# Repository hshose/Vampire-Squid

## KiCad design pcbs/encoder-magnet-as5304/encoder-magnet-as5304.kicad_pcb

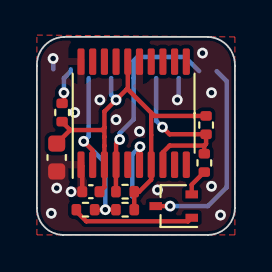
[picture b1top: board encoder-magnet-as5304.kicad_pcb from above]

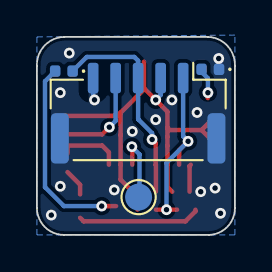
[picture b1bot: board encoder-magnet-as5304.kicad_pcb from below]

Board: 2 copper layers, 11.0 x 11.0 mm, 14 parts (4 on the bottom side), 10 nets.

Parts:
C1: 100n; C_0402_1005Metric
C2: 10µ; C_0603_1608Metric
D1: Red; LED_0402_1005Metric
D2: Blue; LED_0402_1005Metric
J1: BM05B-GHS; JST_GH_BM05B-GHS-TBT_1x05-1MP_P1.25mm_Vertical
Q1: BC807-40LWX; SOT-323_SC-70
R1, R2, R3: 1k; R_0402_1005Metric
R4: 47k; R_0402_1005Metric
R5, R6: 4k7; R_0402_1005Metric
TP1: AGC out; TestPoint_Pad_D1.5mm
U1: AS5304; TSSOP-20_4.4x6.5mm_P0.65mm

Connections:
+5V: C1.1, C2.1, J1.2, R1.1, R2.1, R3.1, R6.1, U1.3 (VDDP), U1.7 (VDD), U1.16 (VDDA)
/A: J1.1, R1.2, R4.1, U1.2 (A)
/B: D1.1 (K), J1.3, R2.2, U1.4 (B)
/I: J1.4, R3.2, R5.1, U1.8 (I)
GND: C1.2, C2.2, D2.1 (K), J1.5, J1.MP (MountPin), U1.1 (VSS), U1.15 (TEST_GND), U1.20 (ZPZ)
unnamed: D1.2 (A), Q1.3 (C)
unnamed: D2.2 (A), R6.2
unnamed: Q1.1 (B), R4.2
unnamed: Q1.2 (E), R5.2
unnamed: TP1.1, U1.6 (AO)

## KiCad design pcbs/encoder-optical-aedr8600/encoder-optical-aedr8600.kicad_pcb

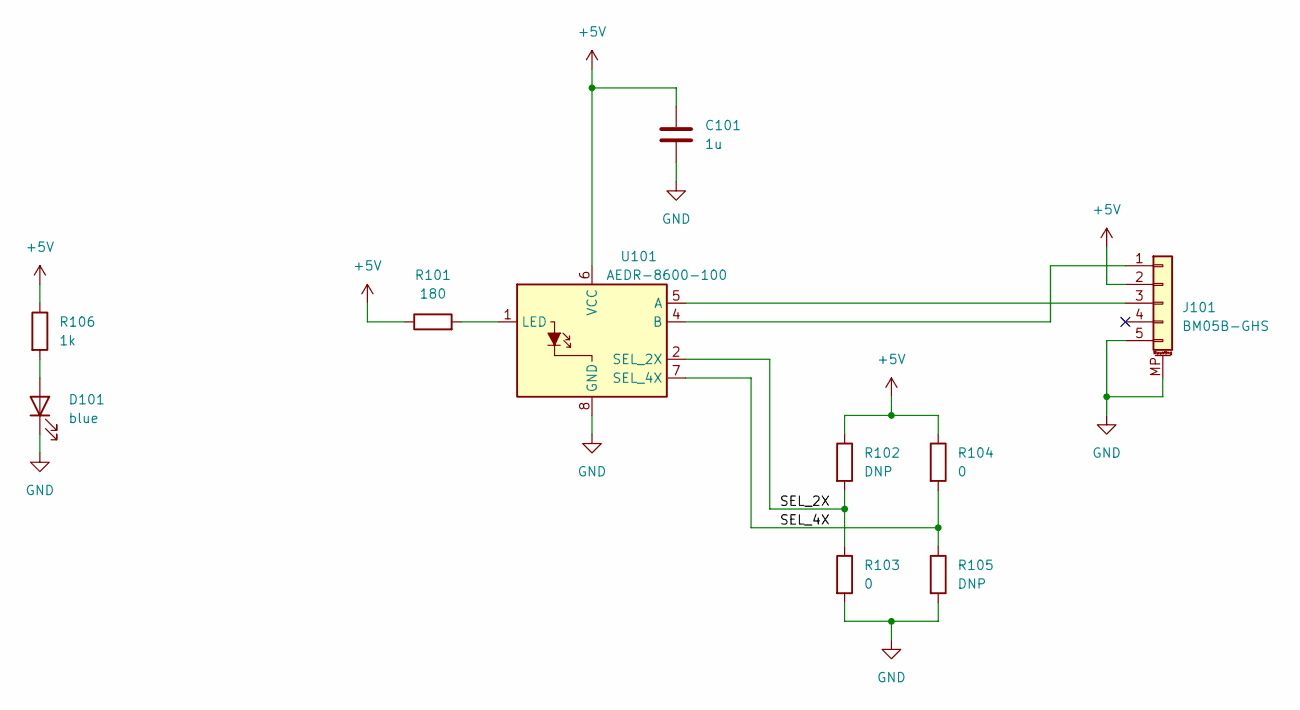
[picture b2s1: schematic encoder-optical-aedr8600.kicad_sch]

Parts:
C101: 1u; C_0402_1005Metric
D101: blue; LED_0402_1005Metric
J101: BM05B-GHS; JST_GH_BM05B-GHS-TBT_1x05-1MP_P1.25mm_Vertical
R101: 180; R_0402_1005Metric
R102, R105: DNP; R_0402_1005Metric
R103, R104: 0; R_0402_1005Metric
R106: 1k; R_0402_1005Metric
U101: AEDR-8600-100; AEDR-8600

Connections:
+5V: C101.1, J101.2, R101.1, R102.1, R104.1, R106.1, U101.6 (VCC)
/SEL_2X: R102.2, R103.1, U101.2 (SEL_2X)
/SEL_4X: R104.2, R105.1, U101.7 (SEL_4X)
GND: C101.2, D101.1 (K), J101.5, J101.MP (MountPin), R103.2, R105.2, U101.8 (GND)
unnamed: D101.2 (A), R106.2
unnamed: J101.1, U101.4 (B)
unnamed: J101.3, U101.5 (A)
unnamed: R101.2, U101.1 (LED)

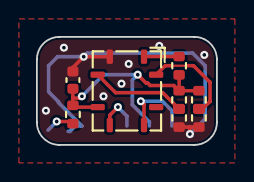
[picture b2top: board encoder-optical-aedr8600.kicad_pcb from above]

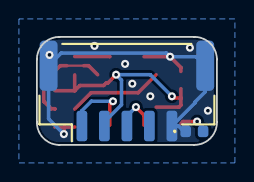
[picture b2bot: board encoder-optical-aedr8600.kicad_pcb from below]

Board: 2 copper layers, 10.0 x 6.0 mm, 10 parts (2 on the bottom side), 8 nets.

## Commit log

2021-11-04 Improve wheel draft
2021-11-06 Restructure repo
2021-11-06 Add gitignore
2021-11-06 Create AEDR-8600 symbol
2021-11-06 Create footprint for AEDR-8600 encoder chip
2021-11-06 Create PCB encoder-optical-aedr8600
2021-11-07 AEDR-8600 freecad and step model
2021-11-07 gitignore: FreeCAD ignores added
2021-11-07 Finish encoder-optical-aedr8600 PCB layout
2021-11-07 Export encoder-optical-aedr8600 3D model (STEP)
2021-11-07 Increase outline corner radius
2021-11-07 Add encoder wheel "PCB"
2021-11-07 encoder-wheel-1 PCB: Export step
2021-11-07 encoder-optical-aedr8600: Add panelized PCB
2021-11-07 [wip] drive cad
2021-11-07 [wip] roller to ballbearing to fit 6110
2021-11-09 [wip] drive body frame attach
2021-11-13 [wip] mechanical robot concept
2021-11-20 [cad] drive assembly
2021-11-20 [cad] removed old drive w/o assembly
2021-11-20 [cad] initial commit on chassis
2021-11-20 [cad] initial commit on robot assembly
2021-11-23 [cad] wip on wheel drive
2021-11-23 Encoder wheel für Filmbelichtung angepasst und exportiert
2021-12-19 AS5304 magnet encoder PCB
2021-12-19 Fix AS5304 board dimensions
2021-12-19 Fix ground plane dimensions for panelization tool
2021-12-19 Add panelized PCB for AS5304 magnet encoder
2021-12-19 Add readme for AS5304 panel creation
2021-12-23 Manually redraw broken outline for panelized AS5304 PCB
2022-01-02 [cad] assembly workbench for drive
2022-01-02 [cad] removed old cq attempt
2023-02-18 Add script to generate KiCAD pcb file for enc. wheel with magnets
2023-02-18 Update magnet diameter and add KiCAD pcb file
2023-02-18 Add marker for every second magnet and mark quarter of the circle
2023-02-18 Add MANUALLY a "GND" Layer to the (before generated) pcb file
2023-02-18 Add gerber export
2023-03-10 magnet encoder pcb 1.45 and 1.40 drill
2023-03-10 new kicad PCB file
